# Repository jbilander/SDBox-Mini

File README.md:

# SDBox Mini for Amiga
SDBox in a standard DB25 plastic shell

This version is superseded by the new SDBox-v3 here: https://github.com/jbilander/SDBox-v3
***
Rev. 2B <br />

<br />
Video:<br />
https://drive.google.com/file/d/1fLwmIyUeHZX4sln5bpJfz5QkDGD-QTOf/view?usp=sharing
<br />
<br />
+5V taken from floppy port with this USB-C dongle<br />
https://github.com/jbilander/Amiga_DB23_to_USB_C_power_only_adapter
***
Rev. 2A <br />

<br />

***
This hardware uses the firmware written by Niklas Ekström, available here... <br />
https://github.com/niklasekstrom/amiga-par-to-spi-adapter

...or use my fork if you also want the Activity LED to blink (it also includes a batch-script `flashSDBoxMini.bat` for flashing the Mini) <br />
https://github.com/jbilander/amiga-par-to-spi-adapter

***
Connecting the Arduino to program the SDBox Mini

    (Programmer)
    Arduino as ISP - SDBox Mini 
    ------------------------------------
    D13 (SPI) SCK  - Pin 3 (ICSP) SCK
    D12 (SPI) MISO - Pin 1 (ICSP) MISO
    D11 (SPI) MOSI - Pin 4 (ICSP) MOSI
    D10 (SPI) SS   - Pin 5 (ICSP) /RESET
              5V   - Pin 2 VCC
              GND  - Pin 6 GND

On the Nano V3 the pins on the ICSP-header can be utilized connected like below. There is no need to solder an ICSP-header on the mini, you can just hold the connector against the footprint while programming.

***

To use the Arduino Nano as ISP it first has to be flashed with the ArduinoISP-sketch which is available under `File->Examples` in the Arduino IDE, or you can use the attached batch-script `flash_Arduino_as_ISP.bat` and binary hex `ArduinoISP.ino.arduino_standard.hex` I have put them in a zip-file under Releases `ArduinoISP.zip`. Alter the com port in the script file to suit your machine and execute it from a command-prompt. Now you are ready to flash the SDBox-Mini via the Arduino.

***

### Flash the SDBox Mini using the Arduino as ISP
This requires that you already have built the `main.hex` file in the `avr`-folder, then execute `flashSDBoxMini.bat` from a command prompt:
<details>
<summary>

    C:\Users\Jorgen\Projects\amiga-par-to-spi-adapter\avr>flashSDBoxMini.bat

</summary>

```
C:\Users\Jorgen\Projects\amiga-par-to-spi-adapter\avr>"C:\Program Files (x86)\Arduino\hardware\tools\avr/bin/avrdude" -C "C:\Program Files (x86)\Arduino\hardware\tools\avr/etc/avrdude.conf" -v -pm328p -cstk500v1 -PCOM4 -b19200 -Uflash:w:main.hex:i -Ulfuse:w:0xe6:m -Uhfuse:w:0xdf:m -Uefuse:w:0xfc:m

avrdude: Version 6.3-20190619
         Copyright (c) 2000-2005 Brian Dean, http://www.bdmicro.com/
         Copyright (c) 2007-2014 Joerg Wunsch

         System wide configuration file is "C:\Program Files (x86)\Arduino\hardware\tools\avr/etc/avrdude.conf"

         Using Port                    : COM4
         Using Programmer              : stk500v1
         Overriding Baud Rate          : 19200
         AVR Part                      : ATmega328P
         Chip Erase delay              : 9000 us
         PAGEL                         : PD7
         BS2                           : PC2
         RESET disposition             : dedicated
         RETRY pulse                   : SCK
         serial program mode           : yes
         parallel program mode         : yes
         Timeout                       : 200
         StabDelay                     : 100
         CmdexeDelay                   : 25
         SyncLoops                     : 32
         ByteDelay                     : 0
         PollIndex                     : 3
         PollValue                     : 0x53
         Memory Detail                 :

                                  Block Poll               Page                       Polled
           Memory Type Mode Delay Size  Indx Paged  Size   Size #Pages MinW  MaxW   ReadBack
           ----------- ---- ----- ----- ---- ------ ------ ---- ------ ----- ----- ---------
           eeprom        65    20     4    0 no       1024    4      0  3600  3600 0xff 0xff
           flash         65     6   128    0 yes     32768  128    256  4500  4500 0xff 0xff
           lfuse          0     0     0    0 no          1    0      0  4500  4500 0x00 0x00
           hfuse          0     0     0    0 no          1    0      0  4500  4500 0x00 0x00
           efuse          0     0     0    0 no          1    0      0  4500  4500 0x00 0x00
           lock           0     0     0    0 no          1    0      0  4500  4500 0x00 0x00
           calibration    0     0     0    0 no          1    0      0     0     0 0x00 0x00
           signature      0     0     0    0 no          3    0      0     0     0 0x00 0x00

         Programmer Type : STK500
         Description     : Atmel STK500 Version 1.x firmware
         Hardware Version: 2
         Firmware Version: 1.18
         Topcard         : Unknown
         Vtarget         : 0.0 V
         Varef           : 0.0 V
         Oscillator      : Off
         SCK period      : 0.1 us

avrdude: AVR device initialized and ready to accept instructions

Reading | ################################################## | 100% 0.07s

avrdude: Device signature = 0x1e950f (probably m328p)
avrdude: safemode: lfuse reads as E6
avrdude: safemode: hfuse reads as DF
avrdude: safemode: efuse reads as FC
avrdude: NOTE: "flash" memory has been specified, an erase cycle will be performed
         To disable this feature, specify the -D option.
avrdude: erasing chip
avrdude: reading input file "main.hex"
avrdude: writing flash (496 bytes):

Writing | ################################################## | 100% 0.68s

avrdude: 496 bytes of flash written
avrdude: verifying flash memory against main.hex:
avrdude: load data flash data from input file main.hex:
avrdude: input file main.hex contains 496 bytes
avrdude: reading on-chip flash data:

Reading | ################################################## | 100% 0.44s

avrdude: verifying ...
avrdude: 496 bytes of flash verified
avrdude: reading input file "0xe6"
avrdude: writing lfuse (1 bytes):

Writing | ################################################## | 100% 0.03s

avrdude: 1 bytes of lfuse written
avrdude: verifying lfuse memory against 0xe6:
avrdude: load data lfuse data from input file 0xe6:
avrdude: input file 0xe6 contains 1 bytes
avrdude: reading on-chip lfuse data:

Reading | ################################################## | 100% 0.02s

avrdude: verifying ...
avrdude: 1 bytes of lfuse verified
avrdude: reading input file "0xdf"
avrdude: writing hfuse (1 bytes):

Writing | ################################################## | 100% 0.02s

avrdude: 1 bytes of hfuse written
avrdude: verifying hfuse memory against 0xdf:
avrdude: load data hfuse data from input file 0xdf:
avrdude: input file 0xdf contains 1 bytes
avrdude: reading on-chip hfuse data:

Reading | ################################################## | 100% 0.02s

avrdude: verifying ...
avrdude: 1 bytes of hfuse verified
avrdude: reading input file "0xfc"
avrdude: writing efuse (1 bytes):

Writing | ################################################## | 100% 0.03s

avrdude: 1 bytes of efuse written
avrdude: verifying efuse memory against 0xfc:
avrdude: load data efuse data from input file 0xfc:
avrdude: input file 0xfc contains 1 bytes
avrdude: reading on-chip efuse data:

Reading | ################################################## | 100% 0.02s

avrdude: verifying ...
avrdude: 1 bytes of efuse verified

avrdude: safemode: lfuse reads as E6
avrdude: safemode: hfuse reads as DF
avrdude: safemode: efuse reads as FC
avrdude: safemode: Fuses OK (E:FC, H:DF, L:E6)

avrdude done.  Thank you.

C:\Users\Jorgen\Projects\amiga-par-to-spi-adapter\avr>

```
</details>

***

### Connecting a RPi4 to program the SDBox Mini

<br />
Warning!<br />
Connection of a GPIO to a voltage higher than 3.3V will likely destroy the GPIO block within the SoC.<br /><br />
I used my <a href="https://github.com/jbilander/Logic-level-converter-board">Logic level converter board</a> in between the devices and powered from the RPi's +5V 
<br />
<br />

<br />
First install avrdude:

    sudo apt install avrdude

Now copy the default config file to a new file under /home/pi

    cp /etc/avrdude.conf ~/avrdude_gpio.conf
    
Add this entry last in the file using your editor (vim or nano) and save the file:

    #------------------------------------------------------------
    # Linux GPIO configuration for avrdude
    # Change the lines below to the GPIO pins connected to the AVR
    #------------------------------------------------------------
    programmer
        id        = "pi_1";
        desc      = "Use the Linux sysfs interface to bitbang GPIO lines";
        type      = "linuxgpio";
        reset     = 12;
        sck       = 24;
        mosi      = 23;
        miso      = 18;
    ;

Now cd into /home/pi and make the script-file executable:

    chmod 755 ./flashSDBoxMini.sh

With all jumper-wires connected and `main.hex` built, run the script `flashSDBoxMini.sh` (OR type the line below and hit enter)

    sudo avrdude -C ~/avrdude_gpio.conf -c pi_1 -v -p m328p -Uflash:w:main.hex:i -Ulfuse:w:0xe6:m -Uhfuse:w:0xdf:m -Uefuse:w:0xfc:m

<details>
<summary>

    pi@raspberrypi:~ $ ./flashSDBoxMini.sh

</summary>

```
avrdude: Version 6.3-20171130
         Copyright (c) 2000-2005 Brian Dean, http://www.bdmicro.com/
         Copyright (c) 2007-2014 Joerg Wunsch

         System wide configuration file is "/home/pi/avrdude_gpio.conf"
         User configuration file is "/root/.avrduderc"
         User configuration file does not exist or is not a regular file, skipping

         Using Port                    : unknown
         Using Programmer              : pi_1
         AVR Part                      : ATmega328P
         Chip Erase delay              : 9000 us
         PAGEL                         : PD7
         BS2                           : PC2
         RESET disposition             : dedicated
         RETRY pulse                   : SCK
         serial program mode           : yes
         parallel program mode         : yes
         Timeout                       : 200
         StabDelay                     : 100
         CmdexeDelay                   : 25
         SyncLoops                     : 32
         ByteDelay                     : 0
         PollIndex                     : 3
         PollValue                     : 0x53
         Memory Detail                 :

                                  Block Poll               Page                       Polled
           Memory Type Mode Delay Size  Indx Paged  Size   Size #Pages MinW  MaxW   ReadBack
           ----------- ---- ----- ----- ---- ------ ------ ---- ------ ----- ----- ---------
           eeprom        65    20     4    0 no       1024    4      0  3600  3600 0xff 0xff
           flash         65     6   128    0 yes     32768  128    256  4500  4500 0xff 0xff
           lfuse          0     0     0    0 no          1    0      0  4500  4500 0x00 0x00
           hfuse          0     0     0    0 no          1    0      0  4500  4500 0x00 0x00
           efuse          0     0     0    0 no          1    0      0  4500  4500 0x00 0x00
           lock           0     0     0    0 no          1    0      0  4500  4500 0x00 0x00
           calibration    0     0     0    0 no          1    0      0     0     0 0x00 0x00
           signature      0     0     0    0 no          3    0      0     0     0 0x00 0x00

         Programmer Type : linuxgpio
         Description     : Use the Linux sysfs interface to bitbang GPIO lines
         Pin assignment  : /sys/class/gpio/gpio{n}
           RESET   =  12
           SCK     =  24
           MOSI    =  23
           MISO    =  18

avrdude: AVR device initialized and ready to accept instructions

Reading | ################################################## | 100% 0.00s

avrdude: Device signature = 0x1e950f (probably m328p)
avrdude: safemode: lfuse reads as E6
avrdude: safemode: hfuse reads as DF
avrdude: safemode: efuse reads as FC
avrdude: NOTE: "flash" memory has been specified, an erase cycle will be performed
         To disable this feature, specify the -D option.
avrdude: erasing chip
avrdude: reading input file "main.hex"
avrdude: writing flash (496 bytes):

Writing | ################################################## | 100% 0.11s

avrdude: 496 bytes of flash written
avrdude: verifying flash memory against main.hex:
avrdude: load data flash data from input file main.hex:
avrdude: input file main.hex contains 496 bytes
avrdude: reading on-chip flash data:

Reading | ################################################## | 100% 0.10s

avrdude: verifying ...
avrdude: 496 bytes of flash verified
avrdude: reading input file "0xe6"
avrdude: writing lfuse (1 bytes):

Writing | ################################################## | 100% 0.00s

avrdude: 1 bytes of lfuse written
avrdude: verifying lfuse memory against 0xe6:
avrdude: load data lfuse data from input file 0xe6:
avrdude: input file 0xe6 contains 1 bytes
avrdude: reading on-chip lfuse data:

Reading | ################################################## | 100% 0.00s

avrdude: verifying ...
avrdude: 1 bytes of lfuse verified
avrdude: reading input file "0xdf"
avrdude: writing hfuse (1 bytes):

Writing | ################################################## | 100% 0.00s

avrdude: 1 bytes of hfuse written
avrdude: verifying hfuse memory against 0xdf:
avrdude: load data hfuse data from input file 0xdf:
avrdude: input file 0xdf contains 1 bytes
avrdude: reading on-chip hfuse data:

Reading | ################################################## | 100% 0.00s

avrdude: verifying ...
avrdude: 1 bytes of hfuse verified
avrdude: reading input file "0xfc"
avrdude: writing efuse (1 bytes):

Writing | ################################################## | 100% 0.00s

avrdude: 1 bytes of efuse written
avrdude: verifying efuse memory against 0xfc:
avrdude: load data efuse data from input file 0xfc:
avrdude: input file 0xfc contains 1 bytes
avrdude: reading on-chip efuse data:

Reading | ################################################## | 100% 0.00s

avrdude: verifying ...
avrdude: 1 bytes of efuse verified

avrdude: safemode: lfuse reads as E6
avrdude: safemode: hfuse reads as DF
avrdude: safemode: efuse reads as FC
avrdude: safemode: Fuses OK (E:FC, H:DF, L:E6)

avrdude done.  Thank you.

pi@raspberrypi:~ $

```
</details>

***

### Caveats

One caveat to keep in mind when building and programming Rev.2A (the first revision of the Mini) is the flashing of the fw can't be done with U4 chip in place as it drives/conflicts with MISO on ICSP (In-Circuit Serial Programming). For Rev. 2B PCB use 74AHCT1G126 instead of 74LVC1G17, same package/footprint. This solves the flashing conflict problem. You put a Jumper-shunt on JP1 (on Rev 2B PCB) while flashing and remove it afterwards.

***

### Building SDBox Mini

Start with the 16 MHz Crystal, C8, C9 and the ATMega328P. 

***

At this point you should be able to flash the Firmware to the ATMega using either an Arduino as ISP or a Raspberry Pi.<br /><br />

Continue with the rest of the components on the front side, and then the back side. I usually pre-tin the C1 pads and use hot air to put the C1-Capacitor in place.
***

***

Verify the Micro USB-jack and the voltage levels...

***

***

Now it's time to drill the holes for the LEDs, begin with a 1 mm drill and then step up to 2 mm and finally 3 mm. Be very careful when drilling to get a nice clean 3mm hole, it's very easy to slip and the hole gets oval or offset.

***

***

Short video showing copying a 8 MB file from the HD to the SD-card on my A1200. +5V to power the SDBox I nicked from the floppy port DB23->microUSB (Howto make such a cable <a href="https://github.com/jbilander/SDBox-v2#howto-get-5v-from-the-amigas-external-floppy-port-250-ma-max-lets-make-a-cable">here</a> ).
<br />
Video:<br />
https://i.imgur.com/mF9Bp4C.mp4

***

***

### Amiga installation:

Download `Amiga.zip` from Releases.

* Put latest `fat95` into `L:`  (download from Aminet)
* Put `SD0` and `SD0.info` into `Devs:`  (from `Amiga.zip`)
* Put `spisd.device` into `Devs:` (from `Amiga.zip`)
* Put `Mount_SDCARD` and `Mount_SDCARD.info` anywhere on your HD or floppy disk.
* Put a FAT/FAT32 formatted MicroSD-card in the card reader (Max 4 GB partitioned).
* Double-click the `Mount_SDCARD` icon.

Disk icon should now appear on the Workbench screen.

***

Happy Hackin´

***
BOM Rev. 2B  (Same as 2A with the addition)
---------
Position  | Name/Value   | Package | Notes
-|-|-|-|
U4 | 74AHCT1G126 | 5-TSSOP, SC-70-5, SOT-353  (2.0 mm × 1.25mm) | Single non-inverting buffer 74AHCT1G126 (instead of 74LVC1G17) https://www.mouser.com/ProductDetail/Nexperia/74AHCT1G126GW125?qs=P62ublwmbi%252BsCpFPoi5fgw%3D%3D 
JP1 | 2.0mm two-pin header + jumper-shunt | |
R6 | 10k Ohm Resistor | 0603 SMD | Pull-up resistor for OE pin 1 of 74AHCT1G126

***

BOM Rev. 2A
---------
Position  | Name/Value   | Package | Notes
-|-|-|-|
U1 | LM1117-3.3 | SOT-223 | Low-Dropout Linear Regulator 3.3 Volt
U2 | ATMega328P-AU | TQFP-32_7x7mm_P0.8mm | 8-bit AVR Microcontroller with 32K Bytes In-System Programmable Flash
U3 | 74LVC3G17 | TSSOP-8_3x3mm_P0.65mm | Triple non-inverting Schmitt trigger with 5V tolerant input https://www.digikey.se/product-detail/en/nexperia-usa-inc/74LVC3G17DP-125/1727-5998-1-ND/2753830
U4 | 74LVC1G17 | 5-TSSOP, SC-70-5, SOT-353  (2.0 mm × 1.25mm) | Single non-inverting Schmitt trigger https://www.digikey.se/product-detail/en/nexperia-usa-inc/74LVC1G17GW-125/1727-4117-1-ND/1965408 For Rev. 2B PCB use 74AHCT1G126 instead of 74LVC1G17, same package/footprint: https://www.mouser.com/ProductDetail/Nexperia/74AHCT1G126GW125?qs=P62ublwmbi%252BsCpFPoi5fgw%3D%3D
J1 | D-Sub DB25 | DB25 Male connector with solder lugs | DB25 for Amiga parallel port
J2 | ICSP | PinHeader_2x03_P2.54mm_Vertical | Pin header _(MISO,VCC,SCK,MOSI,/RESET,GND)_ for flashing AVR via In-Circuit Serial Programming
J3 | Micro SD Card Holder | 9-pin Micro SD card slot connector | https://www.aliexpress.com/item/32802051702.html
J4 | Micro USB connector | USB Micro B SMT | For +5V Power only <br />https://www.aliexpress.com/item/32991869539.html
Y1 | Ceramic SMD quartz 16.0 MHz, LC 12 pF | 3 x 5 x 1 mm | For use with XTAL1, XTAL2 on AVR, e.g. https://www.reichelt.com/se/en/ceramic-smd-quartz-3-x-5-x-1-mm-16-0-mhz-16-000000-mj-p85005.html <br /> or <br /> https://www.mouser.se/ProductDetail/520-160-12-30B-AGMT
D1 (Optional) | LED 3mm | PinHeader_1x02_P2.54mm_Vertical, pin pitch 2.54 mm | SD Activity LED indicator, Diffused Orange / Amber, 1.8V-2.3V, 20-30 mA, 605-610nm
D2 (Optional) | LED 3mm | PinHeader_1x02_P2.54mm_Vertical, pin pitch 2.54 mm | Power LED indicator, Green Diffused T-1, 25 mcd, 565 nm, 2.2 V, 25 mA
R1 (Optional) | 150 Ohm Resistor | 0603 SMD, 200 mW | (Mandatory if D1 populated) Series resistor for D1 LED, adjust R-value to your type of LED and preferred brightness
R2 (Optional) | 150 Ohm Resistor | 0603 SMD, 200 mW | (Mandatory if D2 populated) Series resistor for D2 LED, adjust R-value to your type of LED and preferred brightness
R3 | 10k Ohm Resistor | 0603 SMD | Pull-up (to VCC) resistor for /SS
R4 (Optional) | 10k Ohm Resistor | 0603 SMD | Pull-up (to VCC) resistor for MOSI
R5 (Optional) | 10k Ohm Resistor | 0603 SMD | Pull-up (to VCC) resistor for /RESET
RN1 | CAY16-103J4LF RES ARRAY 4 Resistors 10k | 1206 SMD | https://www.digikey.se/product-detail/sv/bourns-inc/CAY16-103J4LF/CAY16-103J4LFCT-ND/
RN1 | | | Pull-up (to 3V3) for MISO_3V3
RN1 | | | Pull-up (to 3V3) for DAT1 pin 8 on MicroSD-holder
RN1 | | | Pull-up (to 3V3) for DAT2 pin 1 on MicroSD-holder
C1 | 220uF Capacitor | SMD-Tantalum, 4.3 x 7.3 x 2.8 mm | Capacitor for VIN +5V Power via USB https://www.reichelt.com/se/en/smd-tantalum-220-f-10v-125-c-t491d-220u-10-p206492.html
C2 | 10uF Capacitor | 1206 SMD | Capacitor (VCC) for Voltage regulator U1
C3 | 10uF Capacitor | 1206 SMD | Capacitor (3V3) for Voltage regulator U1
C4 | 0.1uF = 100nF Capacitor | 0603 SMD | Capacitor (3V3) for Voltage regulator U1
C5 | 0.1uF = 100nF Capacitor | 0603 SMD | Decoupling capacitor for U2
C6 | 0.1uF = 100nF Capacitor | 0603 SMD | Decoupling capacitor for U3
C7 | 0.1uF = 100nF Capacitor | 0603 SMD | Decoupling capacitor for U4
C8 | 16pF Capacitor | 0603 SMD | Capacitor for XTAL1 (Y1)
C9 | 16pF Capacitor | 0603 SMD | Capacitor for XTAL2 (Y1)
X | D-Sub DB25 | Two DB25 plastic shells with screws and nuts | Plastic hood cover x 2

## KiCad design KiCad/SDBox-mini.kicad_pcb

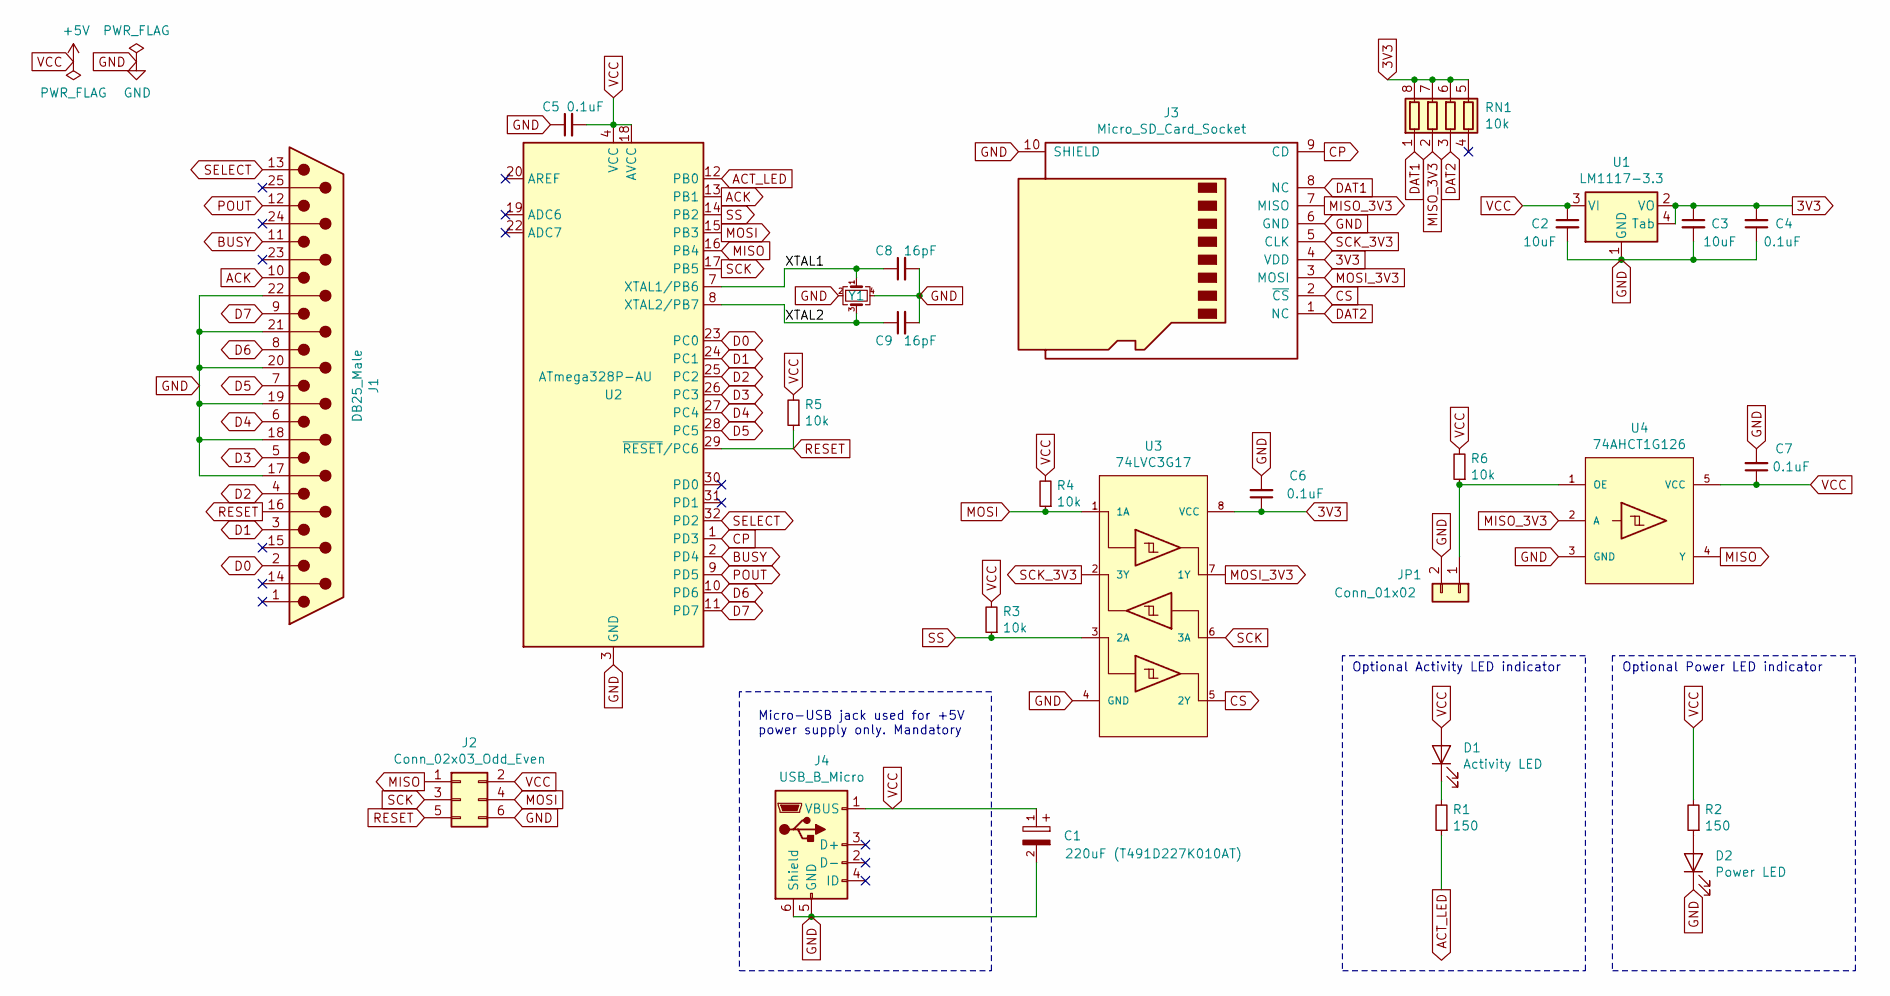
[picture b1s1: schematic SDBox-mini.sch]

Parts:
C1: 220uF (T491D227K010AT); CAPMP7343X430N
C2, C3: 10uF; C_1206_3216Metric_Pad1.42x1.75mm_HandSolder
C4, C5, C6, C7: 0.1uF; C_0603_1608Metric_Pad1.05x0.95mm_HandSolder
C8, C9: 16pF; C_0603_1608Metric_Pad1.05x0.95mm_HandSolder
D1: Activity LED; PinHeader_1x02_P2.54mm_Vertical
D2: Power LED; PinHeader_1x02_P2.54mm_Vertical
J1: DB25_Male; DSUB-25_Male_EdgeMount_P2.77mm
J2: Conn_02x03_Odd_Even; PinHeader_2x03_P2.54mm_Vertical
J3: Micro_SD_Card_Socket; GCT-MEM2055-00-190-01-A
J4: USB_B_Micro; USB_Micro-B_Unknown_5s_SMT
JP1: Conn_01x02; PinHeader_1x02_P2.00mm_Vertical
R1, R2: 150; R_0603_1608Metric_Pad1.05x0.95mm_HandSolder
R3, R4, R5, R6: 10k; R_0603_1608Metric_Pad1.05x0.95mm_HandSolder
RN1: 10k; RESCAF80P320X160X60-8N
U1: LM1117-3.3; SOT-223
U2: ATmega328P-AU; TQFP-32_7x7mm_P0.8mm
U3: 74LVC3G17; TSSOP-8_3x3mm_P0.65mm_Custom_Handsoldering
U4: 74AHCT1G126; SOT-353_SC-70-5_Custom_Handsoldering
Y1: Crystal_GND24_Small; Crystal_EuroQuartz_SMD_4Pin_5.0x3.2mm

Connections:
3V3: C3.1, C4.2, C6.1, J3.4 (VDD), RN1.5 (R4.2), RN1.6 (R3.2), RN1.7 (R2.2), RN1.8 (R1.2), U1.2 (VO), U1.4 (Tab), U3.8 (VCC)
/XTAL1: C8.1, U2.7 (XTAL1/PB6), Y1.1
/XTAL2: C9.1, U2.8 (XTAL2/PB7), Y1.3
ACK: J1.10, U2.13 (PB1)
ACT_LED: R1.1, U2.12 (PB0)
BUSY: J1.11, U2.2 (PD4)
CP: J3.9 (CD), U2.1 (PD3)
CS: J3.2 (~CS), U3.5 (2Y)
D0: J1.2, U2.23 (PC0)
D1: J1.3, U2.24 (PC1)
D2: J1.4, U2.25 (PC2)
D3: J1.5, U2.26 (PC3)
D4: J1.6, U2.27 (PC4)
D5: J1.7, U2.28 (PC5)
D6: J1.8, U2.10 (PD6)
D7: J1.9, U2.11 (PD7)
DAT1: J3.8 (NC), RN1.1 (R1.1)
DAT2: J3.1 (NC), RN1.3 (R3.1)
GND: C1.2, C2.2, C3.2, C4.1, C5.1, C6.2, C7.2, C8.2, C9.2, D2.1 (K), J1.17, J1.18, J1.19, J1.20, J1.21, J1.22, J2.6, J3.6 (GND), J3.10 (SHIELD), J4.5 (GND), J4.6 (Shield), JP1.2, U1.1 (GND), U2.3 (GND), U2.5 (GND), U2.21 (GND), U3.4 (GND), U4.3 (GND), Y1.2, Y1.4
MISO: J2.1, U2.16 (PB4), U4.4 (Y)
MISO_3V3: J3.7 (MISO), RN1.2 (R2.1), U4.2 (A)
MOSI: J2.4, R4.1, U2.15 (PB3), U3.1 (1A)
MOSI_3V3: J3.3 (MOSI), U3.7 (1Y)
unnamed: D1.1 (K), R1.2
unnamed: D2.2 (A), R2.1
unnamed: JP1.1, R6.1, U4.1 (OE)
POUT: J1.12, U2.9 (PD5)
RESET: J1.16, J2.5, R5.1, U2.29 (~RESET~/PC6)
SCK: J2.3, U2.17 (PB5), U3.6 (3A)
SCK_3V3: J3.5 (CLK), U3.2 (3Y)
SELECT: J1.13, U2.32 (PD2)
SS: R3.1, U2.14 (PB2), U3.3 (2A)
VCC: C1.1, C2.1, C5.2, C7.1, D1.2 (A), J2.2, J4.1 (VBUS), R2.2, R3.2, R4.2, R5.2, R6.2, U1.3 (VI), U2.4 (VCC), U2.6 (VCC), U2.18 (AVCC), U4.5 (VCC)

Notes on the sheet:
Optional Activity LED indicator
Optional Power LED indicator
Micro-USB jack used for +5V power supply only. Mandatory

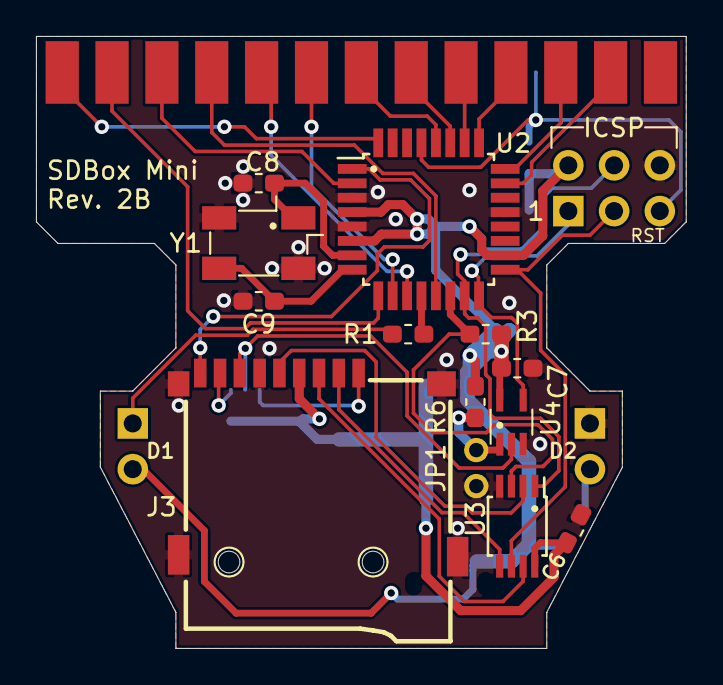
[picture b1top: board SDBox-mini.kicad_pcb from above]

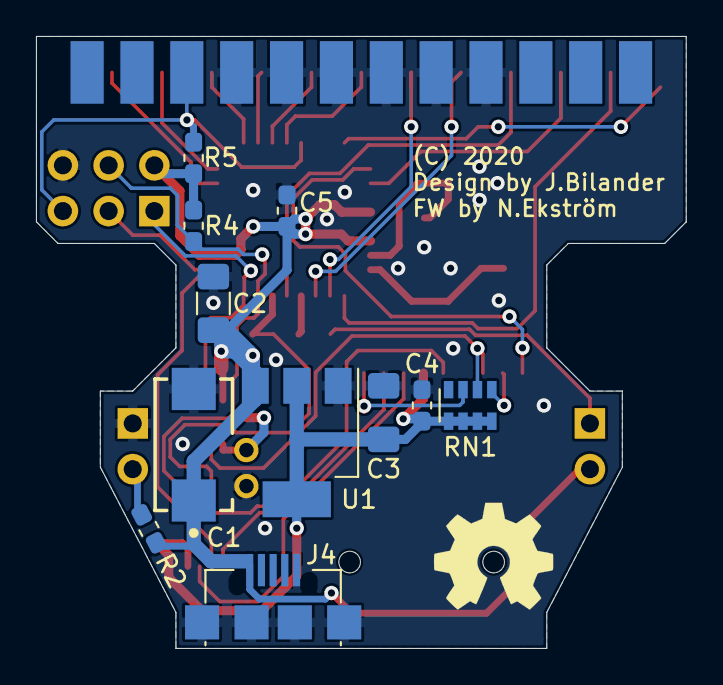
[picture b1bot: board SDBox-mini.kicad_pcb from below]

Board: 2 copper layers, 36.1 x 34.0 mm, 28 parts (11 on the bottom side), 33 nets.

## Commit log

2021-07-18 added KiCad files
2021-07-18 added MicroSD footprint
2021-07-18 resized PCB and added some components
2021-07-19 made custom crystal smd footprint 5.0x3.2mm
2021-07-19 added 3V3 voltage regulator, added 74LVC125A buffer
2021-07-19 added FTDI header
2021-07-19 changed to 74LVC3G17
2021-07-20 added USB micro jack, and Dual non-inverting Schmitt trigger, and debounce circuit for card detect
2021-07-20 adapted for new pinout and rerouted
2021-07-21 imporved routing and small fix of micro-usb footprint
2021-07-21 reshaped PCB outline to accomodate LED indicators
2021-07-22 added footprint for smd tantalum cap T491D227K010AT
2021-07-22 added final caps, completed positioning of components and routing done
2021-07-23 improved GND-stiching and some tracks width
2021-07-23 modified footprint
2021-07-23 silkscreen fix
2021-07-24 added silkscreen texts and oshw-symbol
2021-07-24 added pics
2021-07-24 added schematic pdf
2021-07-26 Changed pin assignment BUSY from PB0 to PD4, POUT from PD4 to PD5 and rerouted due to change in FW.
2021-07-26 removed FTDI-header, added ICSP-header, removed hw-debounce circuit and rerouted
2021-07-26 Improved 3V3 and other small cosmetic fixes
2021-07-27 removed transistor Q1, changed Activity LED circuit to sink by SS
2021-07-27 small via GND improvements
2021-07-27 added decoupling cap near ICSP-header VCC and relabeled ordering of components
2021-07-27 improved GND-area around D6,D7-vias by better positioning
2021-07-27 small fix Activity LED-return line
2021-07-28 removed AREF capacitor, it was unnecessary
2021-07-28 changed Activity-LED to be controlled by PB0, added 10k pull-up resistor on SS-line
2021-07-28 Removed capacitor at VCC-pin ICSP-header and renumbered Caps
2021-07-28 Changed U4 to a 74LVC1G17 and made SOT-353_SC-70-5_Custom_Handsoldering footprint
2021-07-28 adapted TSSOP-8_3x3mm_P0.65mm footprint for Handsoldering
2021-07-29 added optional pull-up on MOSI, fixed keep-out area of copper pour on U3,U4 GND-pads to neighbouring pad
2021-07-30 added common pull-up for DAT1,DAT2-lines (pin 8 and 1) on MicroSD-connector-pads
2021-07-30 added a 10k resistor pack and set individual pull-ups for DAT1,DAT2-lines (pin 8,1)
2021-08-01 update schematic pdf
2021-08-04 Fixed peg holes to 1.2 mm
2021-08-04 Fixed to oval holes and increased from 0.65 mm to 1 mm in y-direction, accomodates 0.7mm pegs
2021-08-04 cleanup of lib symbols and pcb silkscreen text
2021-08-04 update of schematic pdf
2021-08-04 Rev2A
2021-08-10 Silkscreen fix marking ICSP pin 1
2021-08-18 updated pics
2021-10-25 added images
2022-05-31 added symbol for 74AHCT1G126
2022-05-31 Replaced U4 (74LVC1G17) with 74AHCT1G126 (same footprint), added pull-up resistor with 2.0mm two-pin-jumper for tristate MISO high-Z when flashing new fw
2022-07-04 Rev2B
2023-08-16 Added pics of SDBox Mini Rev. 2B

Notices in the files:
KiCad/SDBox-mini.kicad_pcb:
(C) 2020
